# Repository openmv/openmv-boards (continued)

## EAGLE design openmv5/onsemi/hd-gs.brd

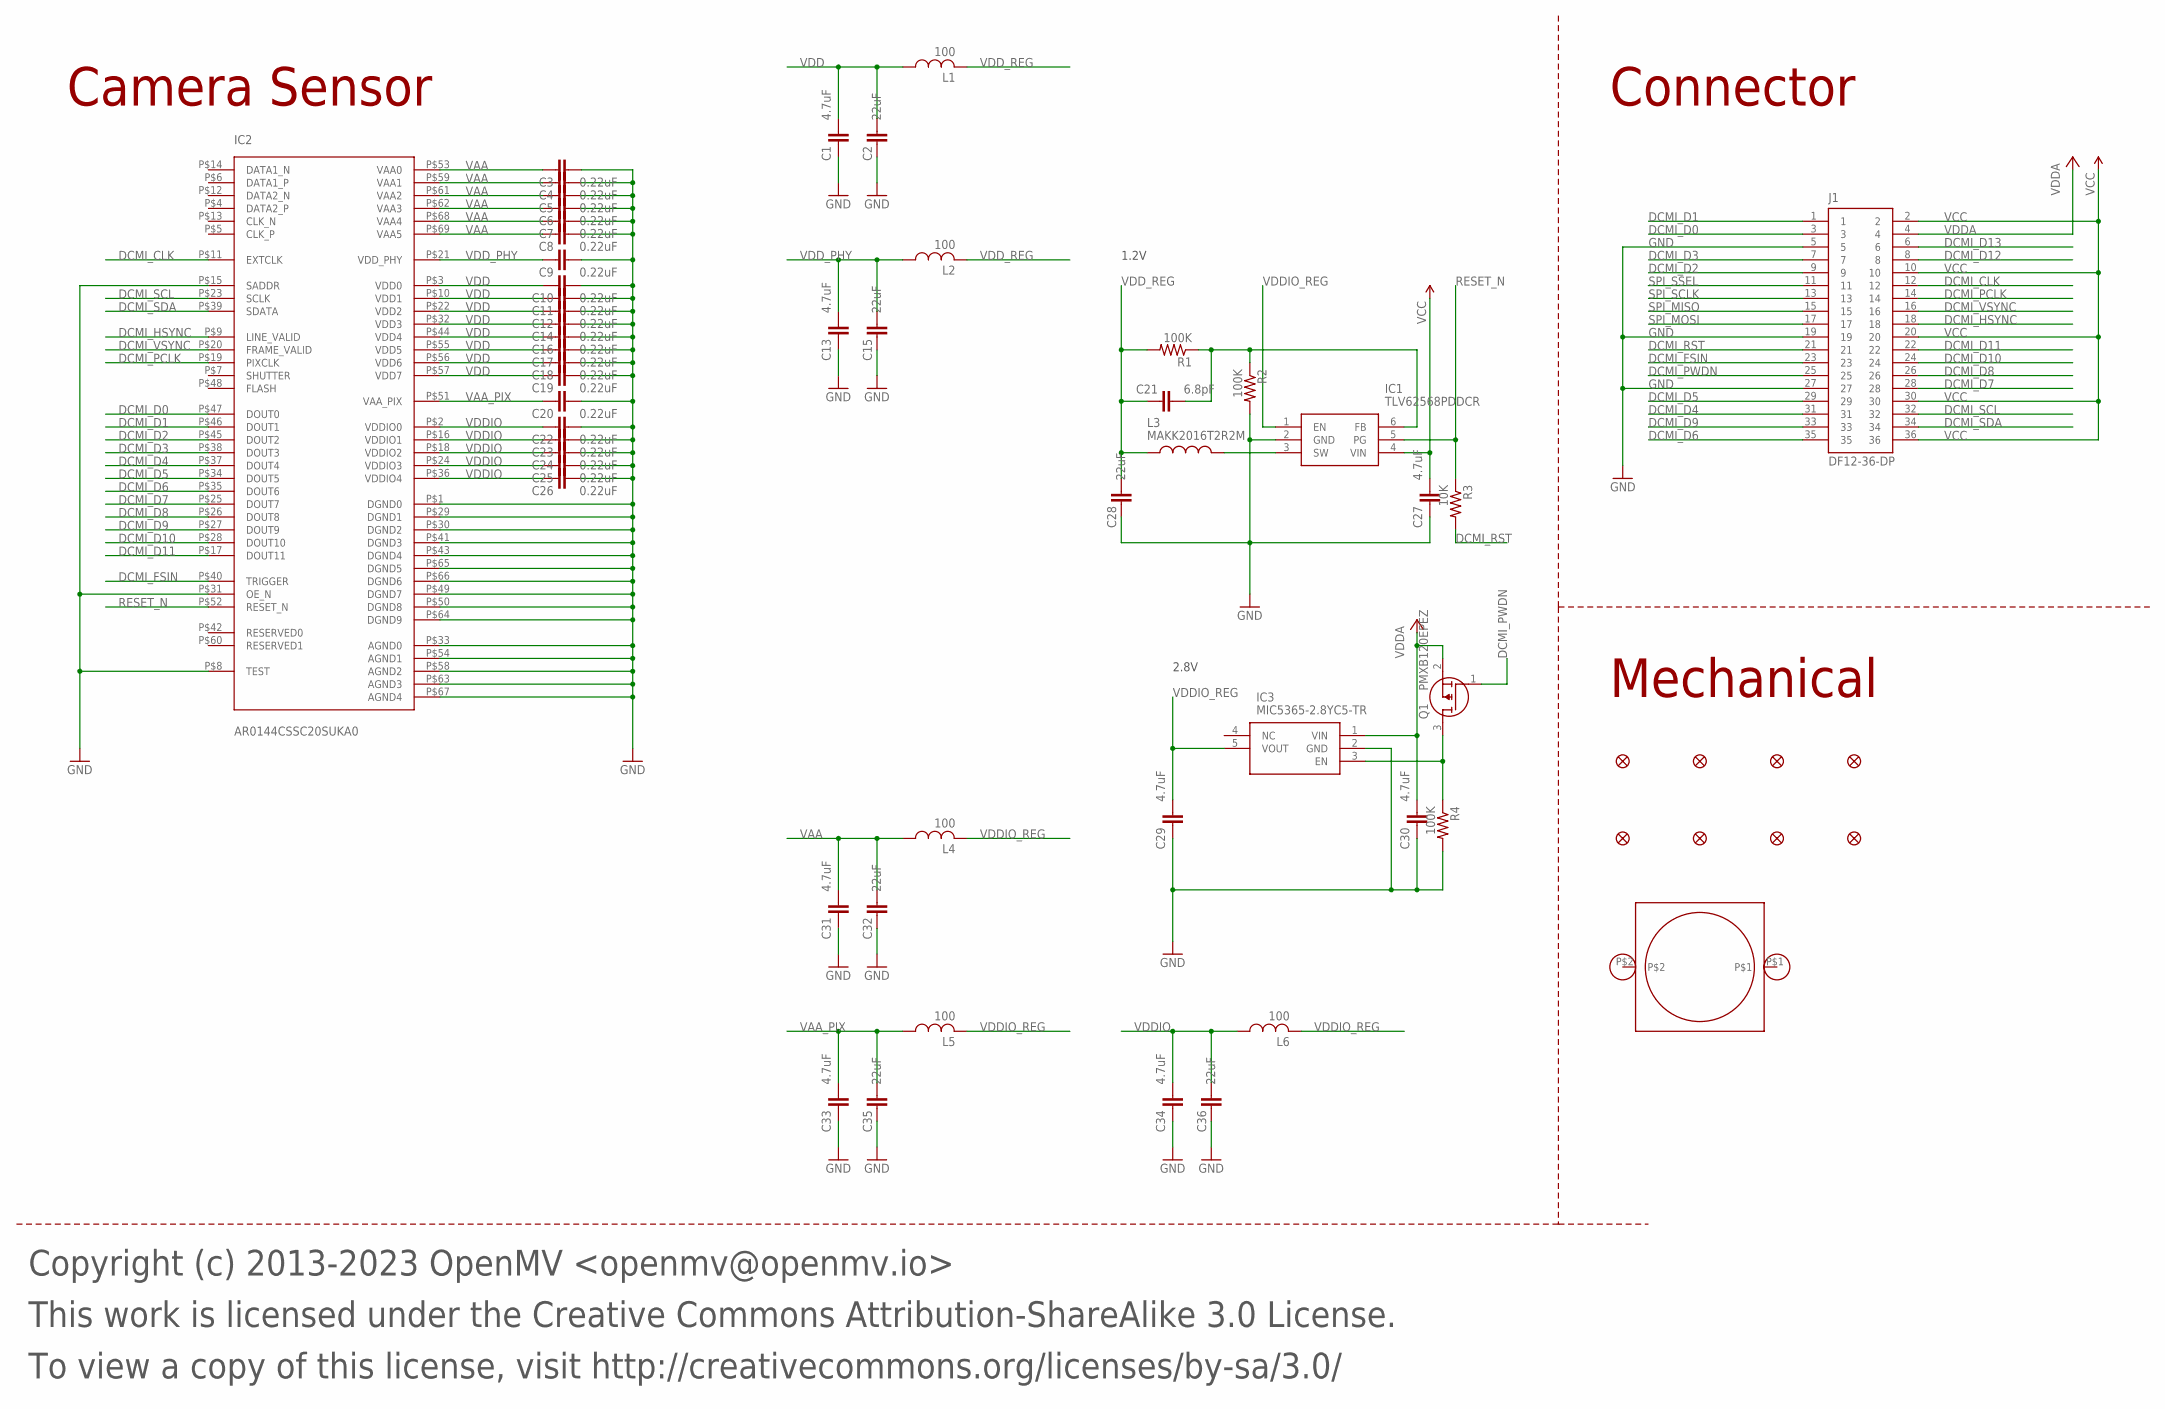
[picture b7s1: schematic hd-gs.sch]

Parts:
C1, C13, C27, C29, C30, C31, C33, C34: 4.7uF; 0402; MPN JMK105BBJ475MV-F
C2, C15, C28, C32, C35, C36: 22uF; 0805; MPN CL21A226MQQNNNE
C3, C4, C5, C6, C7, C8, C9, C10, C11, C12, C14, C16, C17, C18, C19, C20, C22, C23, C24, C25, C26: 0.22uF; C0201; MPN GRM033R60J224ME15D
C21: 6.8pF; 0402; MPN GRM1555C1H6R8DA01D
FD1, FD2, FD3, FD4, FD5, FD6, FD7, FD8: FIDUCIAL1X2; FIDUCIAL-1X2
H1: LENSMOUNT20MM; LENSMOUNT-20MM
IC1: TLV62568PDDCR; SOT95P280X110-6N; MPN TLV62568PDDCR
IC2: AR0144CSSC20SUKA0; MPN AR0144CSSC20SUKA0-CRBR
IC3: MIC5365-2.8YC5-TR; SOT65P210X110-5N; MPN MIC5365-2.8YC5-TR
J1: DF12-36-DP; MPN DF12NB(3.0)-36DP-0.5V(51)
L1, L2, L4, L5, L6: 100; 0402; MPN MFBM1V1005-101-R
L3: MAKK2016T2R2M; INDC2016X100N; MPN MAKK2016T2R2M
Q1: PMXB120EPEZ; MPN PMXB120EPEZ
R1, R2, R4: 100K; R0402; MPN AC0402FR-07100KL
R3: 10K; R0402; MPN AC0402FR-1310KL

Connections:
DCMI_CLK: IC2.P$11 (EXTCLK), J1.12
DCMI_D0: IC2.P$47 (DOUT0), J1.3
DCMI_D1: IC2.P$46 (DOUT1), J1.1
DCMI_D2: IC2.P$45 (DOUT2), J1.9
DCMI_D3: IC2.P$38 (DOUT3), J1.7
DCMI_D4: IC2.P$37 (DOUT4), J1.31
DCMI_D5: IC2.P$34 (DOUT5), J1.29
DCMI_D6: IC2.P$35 (DOUT6), J1.35
DCMI_D7: IC2.P$25 (DOUT7), J1.28
DCMI_D8: IC2.P$26 (DOUT8), J1.26
DCMI_D9: IC2.P$27 (DOUT9), J1.33
DCMI_D10: IC2.P$28 (DOUT10), J1.24
DCMI_D11: IC2.P$17 (DOUT11), J1.22
DCMI_D12: J1.8
DCMI_D13: J1.6
DCMI_FSIN: IC2.P$40 (TRIGGER), J1.23
DCMI_HSYNC: IC2.P$9 (LINE_VALID), J1.18
DCMI_PCLK: IC2.P$19 (PIXCLK), J1.14
DCMI_PWDN: J1.25, Q1.1 (G)
DCMI_PWDN_INT: IC3.3 (EN), Q1.3 (D), R4.1
DCMI_RST: J1.21, R3.2
DCMI_SCL: IC2.P$23 (SCLK), J1.32
DCMI_SDA: IC2.P$39 (SDATA), J1.34
DCMI_VSYNC: IC2.P$20 (FRAME_VALID), J1.16
FB: C21.2, IC1.6 (FB), R1.1, R2.1
GND: C1.1, C2.1, C3.2, C4.2, C5.2, C6.2, C7.2, C8.2, C9.2, C10.2, C11.2, C12.2, C13.1, C14.2, C15.1, C16.2, C17.2, C18.2, C19.2, C20.2, C22.2, C23.2, C24.2, C25.2, C26.2, C27.1, C28.1, C29.1, C30.1, C31.1, C32.1, C33.1, C34.1, C35.1, C36.1, IC1.2 (GND), IC2.P$1 (DGND0), IC2.P$8 (TEST), IC2.P$15 (SADDR), IC2.P$29 (DGND1), IC2.P$30 (DGND2), IC2.P$31 (OE_N), IC2.P$33 (AGND0), IC2.P$41 (DGND3), IC2.P$43 (DGND4), IC2.P$49 (DGND7), IC2.P$50 (DGND8), IC2.P$54 (AGND1), IC2.P$58 (AGND2), IC2.P$63 (AGND3), IC2.P$64 (DGND9), IC2.P$65 (DGND5), IC2.P$66 (DGND6), IC2.P$67 (AGND4), IC3.2 (GND), J1.5, J1.19, J1.27, R2.2, R4.2
RESET_N: IC1.5 (PG), IC2.P$52 (RESET_N), R3.1
SPI_MISO: J1.15
SPI_MOSI: J1.17
SPI_SCLK: J1.13
SPI_SSEL: J1.11
SW: IC1.3 (SW), L3.2
VAA: C3.1, C4.1, C5.1, C6.1, C7.1, C8.1, C31.2, C32.2, IC2.P$53 (VAA0), IC2.P$59 (VAA1), IC2.P$61 (VAA2), IC2.P$62 (VAA3), IC2.P$68 (VAA4), IC2.P$69 (VAA5), L4.1
VAA_PIX: C20.1, C33.2, C35.2, IC2.P$51 (VAA_PIX), L5.1
VCC: C27.2, IC1.4 (VIN), J1.2, J1.10, J1.20, J1.30, J1.36
VDD: C1.2, C2.2, C10.1, C11.1, C12.1, C14.1, C16.1, C17.1, C18.1, C19.1, IC2.P$3 (VDD0), IC2.P$10 (VDD1), IC2.P$22 (VDD2), IC2.P$32 (VDD3), IC2.P$44 (VDD4), IC2.P$55 (VDD5), IC2.P$56 (VDD6), IC2.P$57 (VDD7), L1.1
VDDA: C30.2, IC3.1 (VIN), J1.4, Q1.2 (S)
VDDIO: C22.1, C23.1, C24.1, C25.1, C26.1, C34.2, C36.2, IC2.P$2 (VDDIO0), IC2.P$16 (VDDIO1), IC2.P$18 (VDDIO2), IC2.P$24 (VDDIO3), IC2.P$36 (VDDIO4), L6.1
VDDIO_REG: C29.2, IC1.1 (EN), IC3.5 (VOUT), L4.2, L5.2, L6.2
VDD_PHY: C9.1, C13.2, C15.2, IC2.P$21 (VDD_PHY), L2.1
VDD_REG: C21.1, C28.2, L1.2, L2.2, L3.1, R1.2

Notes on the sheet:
Copyright (c) 2013-2023 OpenMV <openmv@openmv.io>
This work is licensed under the Creative Commons Attribution-ShareAlike 3.0 License.
To view a copy of this license, visit http://creativecommons.org/licenses/by-sa/3.0/
Camera Sensor
Mechanical
Connector
1.2V
2.8V

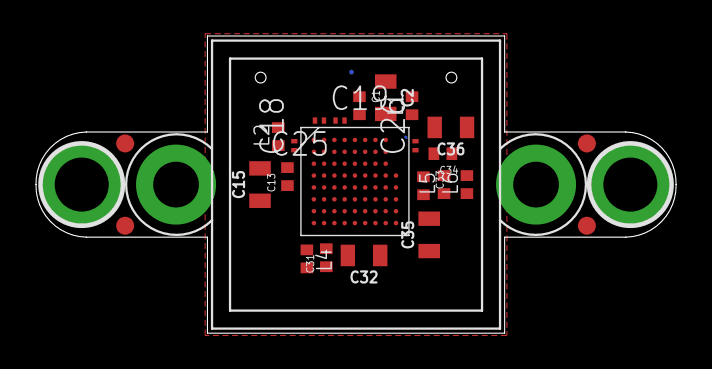
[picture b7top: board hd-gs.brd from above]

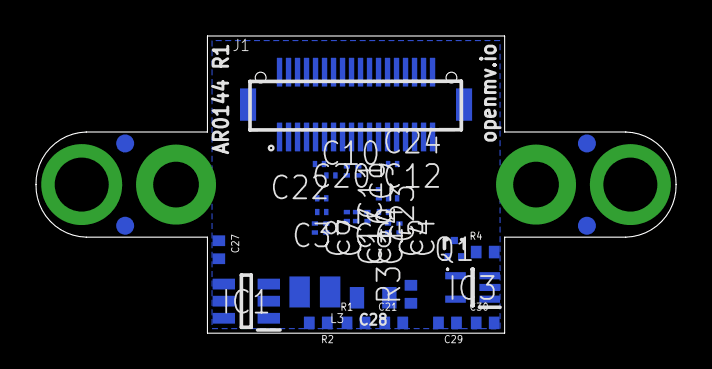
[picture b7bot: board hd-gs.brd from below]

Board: 6 copper layers, 35.6 x 16.5 mm, 60 parts (35 on the bottom side), 35 nets.

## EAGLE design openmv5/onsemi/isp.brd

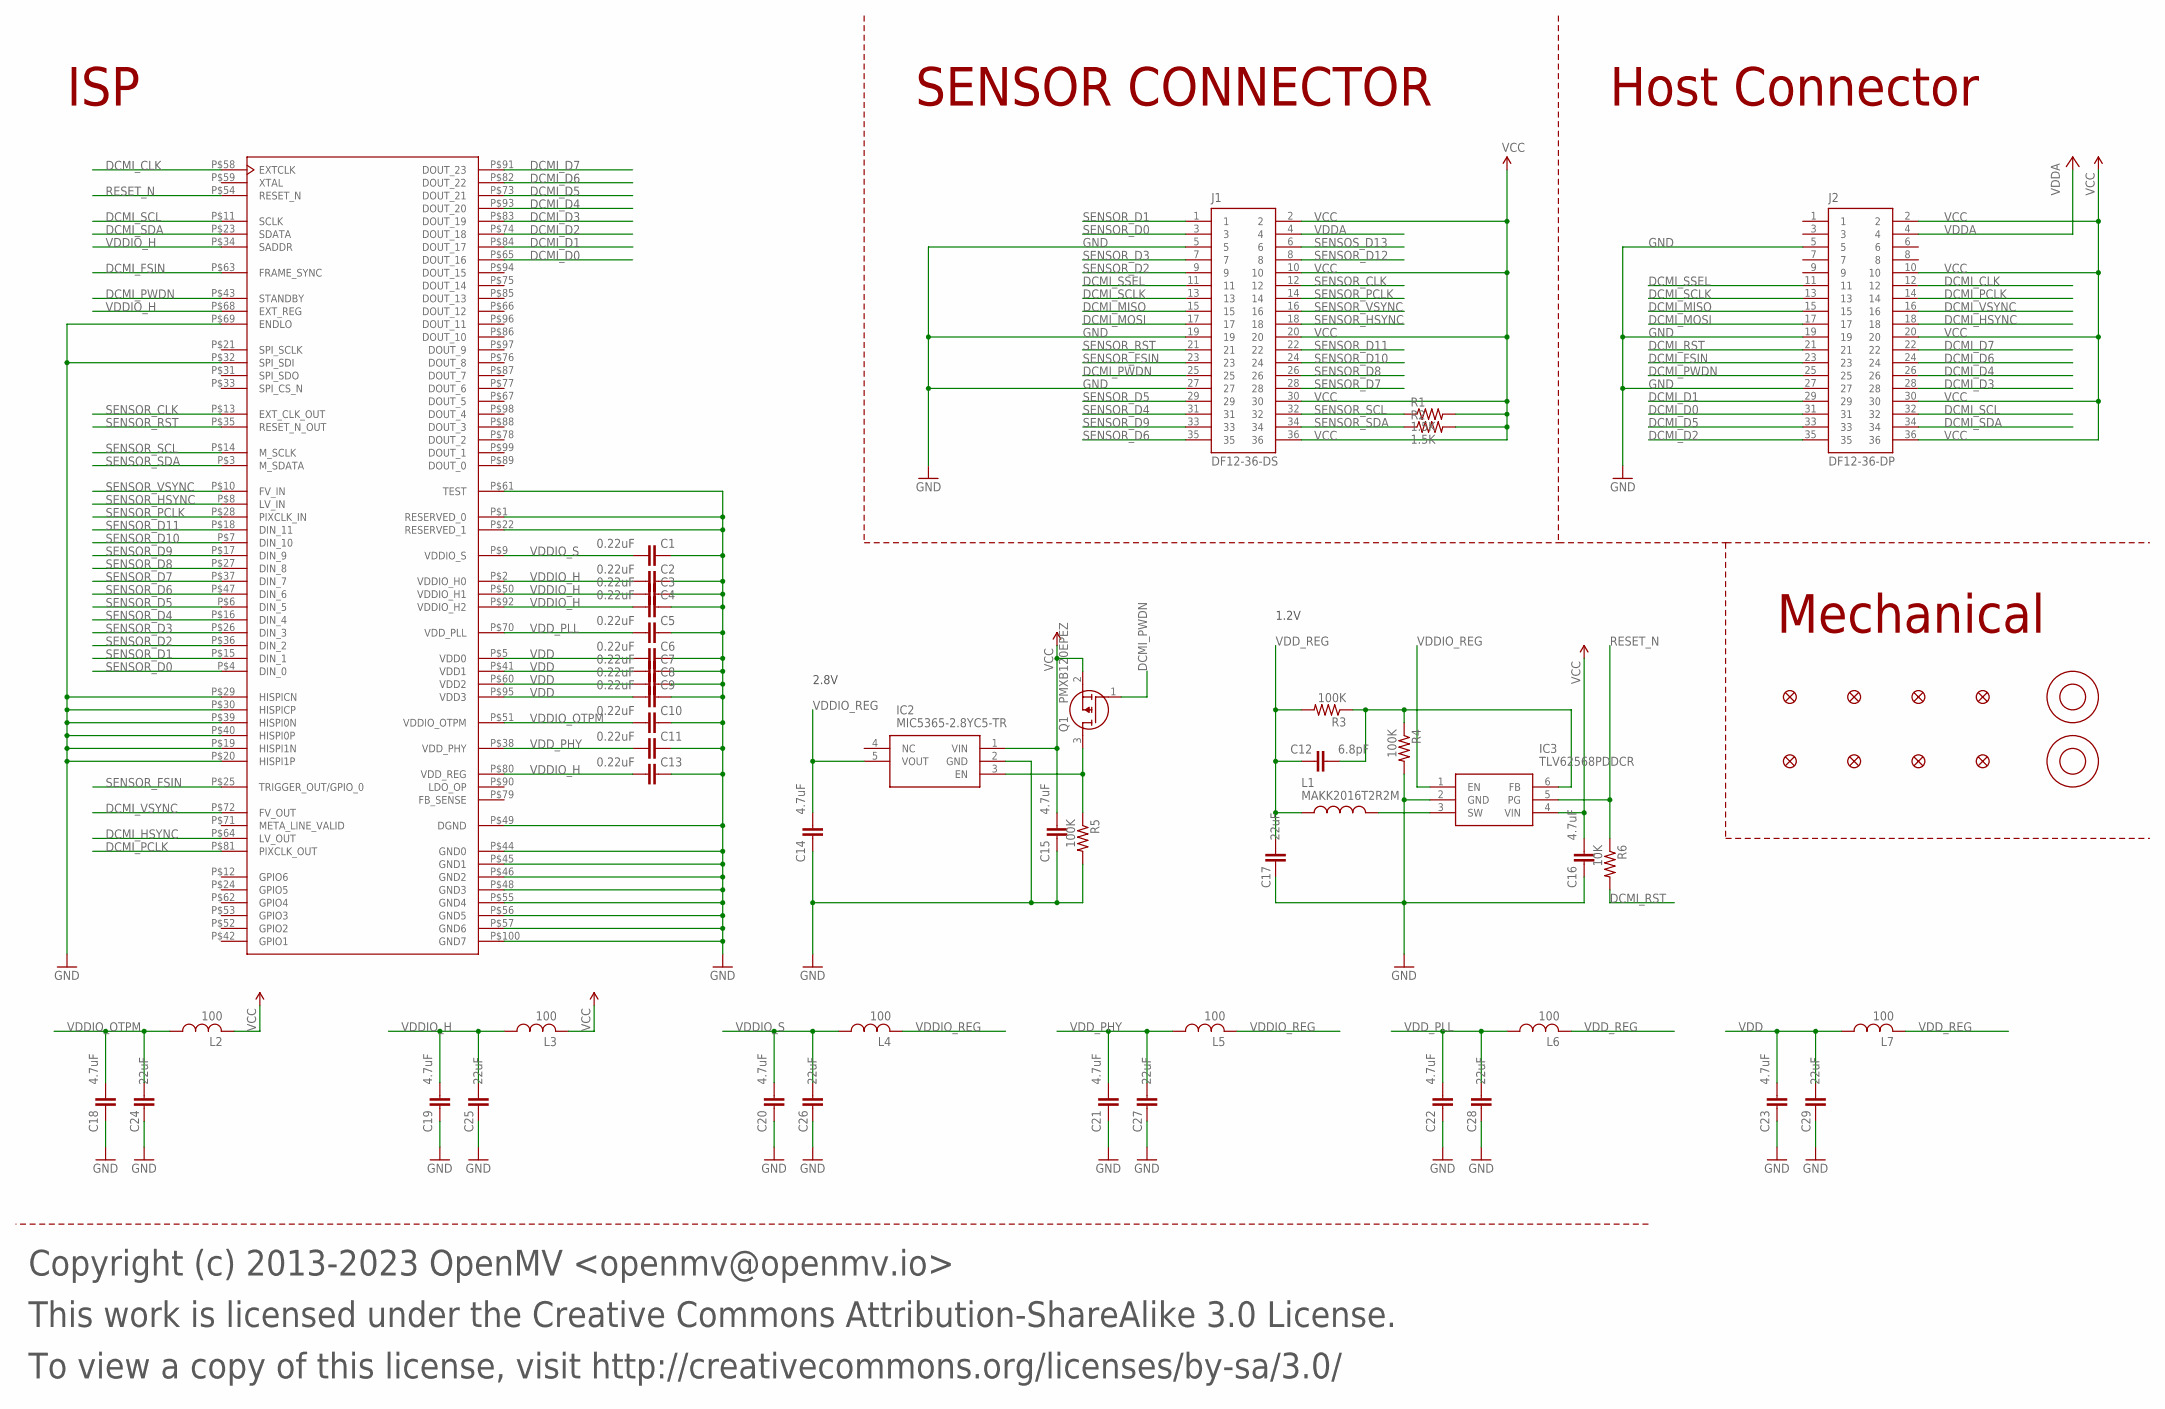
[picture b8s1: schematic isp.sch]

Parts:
C1, C2, C3, C4, C5, C6, C7, C8, C9, C10, C11, C13: 0.22uF; C0201; MPN GRM033R60J224ME15D
C12: 6.8pF; 0402; MPN GRM1555C1H6R8DA01D
C14, C15, C16, C18, C19, C20, C21, C22, C23: 4.7uF; 0402; MPN JMK105BBJ475MV-F
C17, C24, C25, C26, C27, C28, C29: 22uF; 0805; MPN CL21A226MQQNNNE
FD1, FD2, FD3, FD4, FD5, FD6, FD7, FD8: FIDUCIAL1X2; FIDUCIAL-1X2
IC1: AP0202AT2L00XPGA0; MPN AP0202AT2L00XPGA0-DR
IC2: MIC5365-2.8YC5-TR; SOT65P210X110-5N; MPN MIC5365-2.8YC5-TR
IC3: TLV62568PDDCR; SOT95P280X110-6N; MPN TLV62568PDDCR
J1: DF12-36-DS; MPN DF12NB-36DS-0.5V(51)
J2: DF12-36-DP; MPN DF12NB(3.0)-36DP-0.5V(51)
L1: MAKK2016T2R2M; INDC2016X100N; MPN MAKK2016T2R2M
L2, L3, L4, L5, L6, L7: 100; 0402; MPN MFBM1V1005-101-R
M1, M2: 9774030151R; MPN 9774030151R
Q1: PMXB120EPEZ; MPN PMXB120EPEZ
R1, R2: 1.5K; R0402; MPN RC0402FR-131K5L
R3, R4, R5: 100K; R0402; MPN AC0402FR-07100KL
R6: 10K; R0402; MPN AC0402FR-1310KL

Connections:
DCMI_CLK: IC1.P$58 (EXTCLK), J2.12
DCMI_D0: IC1.P$65 (DOUT_16), J2.31
DCMI_D1: IC1.P$84 (DOUT_17), J2.29
DCMI_D2: IC1.P$74 (DOUT_18), J2.35
DCMI_D3: IC1.P$83 (DOUT_19), J2.28
DCMI_D4: IC1.P$93 (DOUT_20), J2.26
DCMI_D5: IC1.P$73 (DOUT_21), J2.33
DCMI_D6: IC1.P$82 (DOUT_22), J2.24
DCMI_D7: IC1.P$91 (DOUT_23), J2.22
DCMI_FSIN: IC1.P$63 (FRAME_SYNC), J2.23
DCMI_HSYNC: IC1.P$64 (LV_OUT), J2.18
DCMI_MISO: J1.15, J2.15
DCMI_MOSI: J1.17, J2.17
DCMI_PCLK: IC1.P$81 (PIXCLK_OUT), J2.14
DCMI_PWDN: IC1.P$43 (STANDBY), J1.25, J2.25, Q1.1 (G)
DCMI_PWDN_INT: IC2.3 (EN), Q1.3 (D), R5.1
DCMI_RST: J2.21, R6.2
DCMI_SCL: IC1.P$11 (SCLK), J2.32
DCMI_SCLK: J1.13, J2.13
DCMI_SDA: IC1.P$23 (SDATA), J2.34
DCMI_SSEL: J1.11, J2.11
DCMI_VSYNC: IC1.P$72 (FV_OUT), J2.16
FB: C12.2, IC3.6 (FB), R3.1, R4.1
GND: C1.1, C2.1, C3.1, C4.1, C5.1, C6.1, C7.1, C8.1, C9.1, C10.1, C11.1, C13.1, C14.1, C15.1, C16.1, C17.1, C18.1, C19.1, C20.1, C21.1, C22.1, C23.1, C24.1, C25.1, C26.1, C27.1, C28.1, C29.1, IC1.P$1 (RESERVED_0), IC1.P$19 (HISPI1N), IC1.P$20 (HISPI1P), IC1.P$22 (RESERVED_1), IC1.P$29 (HISPICN), IC1.P$30 (HISPICP), IC1.P$32 (SPI_SDI), IC1.P$39 (HISPI0N), IC1.P$40 (HISPI0P), IC1.P$44 (GND0), IC1.P$45 (GND1), IC1.P$46 (GND2), IC1.P$48 (GND3), IC1.P$49 (DGND), IC1.P$55 (GND4), IC1.P$56 (GND5), IC1.P$57 (GND6), IC1.P$61 (TEST), IC1.P$69 (ENDLO), IC1.P$100 (GND7), IC2.2 (GND), IC3.2 (GND), J1.5, J1.19, J1.27, J2.5, J2.19, J2.27, R4.2, R5.2
RESET_N: IC1.P$54 (RESET_N), IC3.5 (PG), R6.1
SENSOR_CLK: IC1.P$13 (EXT_CLK_OUT), J1.12
SENSOR_D0: IC1.P$4 (DIN_0), J1.3
SENSOR_D1: IC1.P$15 (DIN_1), J1.1
SENSOR_D2: IC1.P$36 (DIN_2), J1.9
SENSOR_D3: IC1.P$26 (DIN_3), J1.7
SENSOR_D4: IC1.P$16 (DIN_4), J1.31
SENSOR_D5: IC1.P$6 (DIN_5), J1.29
SENSOR_D6: IC1.P$47 (DIN_6), J1.35
SENSOR_D7: IC1.P$37 (DIN_7), J1.28
SENSOR_D8: IC1.P$27 (DIN_8), J1.26
SENSOR_D9: IC1.P$17 (DIN_9), J1.33
SENSOR_D10: IC1.P$7 (DIN_10), J1.24
SENSOR_D11: IC1.P$18 (DIN_11), J1.22
SENSOR_D12: J1.8
SENSOR_FSIN: IC1.P$25 (TRIGGER_OUT/GPIO_0), J1.23
SENSOR_HSYNC: IC1.P$8 (LV_IN), J1.18
SENSOR_PCLK: IC1.P$28 (PIXCLK_IN), J1.14
SENSOR_RST: IC1.P$35 (RESET_N_OUT), J1.21
SENSOR_SCL: IC1.P$14 (M_SCLK), J1.32, R1.1
SENSOR_SDA: IC1.P$3 (M_SDATA), J1.34, R2.1
SENSOR_VSYNC: IC1.P$10 (FV_IN), J1.16
SENSOS_D13: J1.6
SW: IC3.3 (SW), L1.2
VCC: C15.2, C16.2, IC2.1 (VIN), IC3.4 (VIN), J1.2, J1.10, J1.20, J1.30, J1.36, J2.2, J2.10, J2.20, J2.30, J2.36, L2.2, L3.2, Q1.2 (S), R1.2, R2.2
VDD: C6.2, C7.2, C8.2, C9.2, C23.2, C29.2, IC1.P$5 (VDD0), IC1.P$41 (VDD1), IC1.P$60 (VDD2), IC1.P$95 (VDD3), L7.1
VDDA: J1.4, J2.4
VDDIO_H: C2.2, C3.2, C4.2, C13.2, C19.2, C25.2, IC1.P$2 (VDDIO_H0), IC1.P$34 (SADDR), IC1.P$50 (VDDIO_H1), IC1.P$68 (EXT_REG), IC1.P$80 (VDD_REG), IC1.P$92 (VDDIO_H2), L3.1
VDDIO_OTPM: C10.2, C18.2, C24.2, IC1.P$51 (VDDIO_OTPM), L2.1
VDDIO_REG: C14.2, IC2.5 (VOUT), IC3.1 (EN), L4.2, L5.2
VDDIO_S: C1.2, C20.2, C26.2, IC1.P$9 (VDDIO_S), L4.1
VDD_PHY: C11.2, C21.2, C27.2, IC1.P$38 (VDD_PHY), L5.1
VDD_PLL: C5.2, C22.2, C28.2, IC1.P$70 (VDD_PLL), L6.1
VDD_REG: C12.1, C17.2, L1.1, L6.2, L7.2, R3.2

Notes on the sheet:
Copyright (c) 2013-2023 OpenMV <openmv@openmv.io>
This work is licensed under the Creative Commons Attribution-ShareAlike 3.0 License.
To view a copy of this license, visit http://creativecommons.org/licenses/by-sa/3.0/
ISP
Mechanical
Host Connector
1.2V
2.8V
SENSOR CONNECTOR

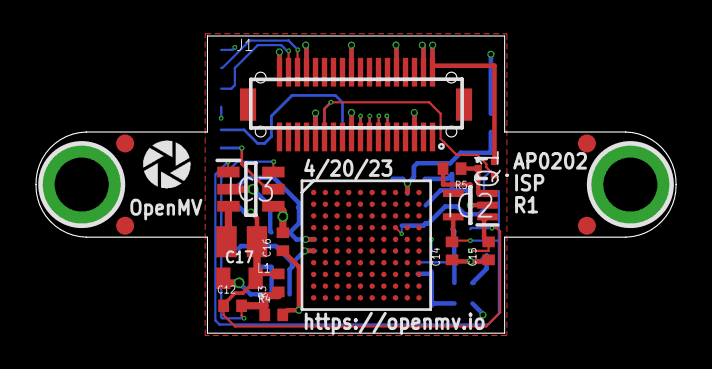
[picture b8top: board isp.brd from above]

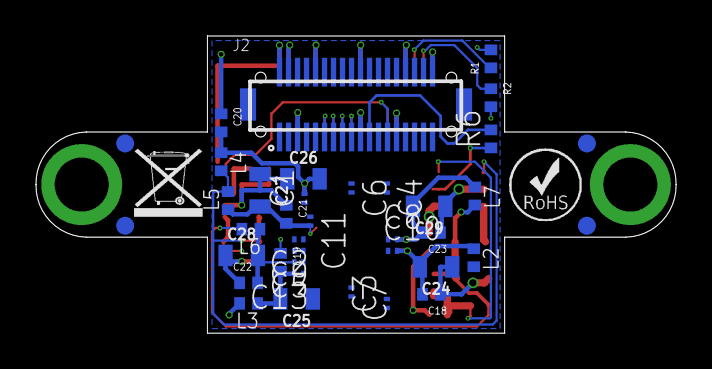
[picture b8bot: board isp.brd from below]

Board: 6 copper layers, 35.6 x 16.5 mm, 61 parts (40 on the bottom side), 56 nets.

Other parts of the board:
U$1: WEEE
U$2: ROHS
U$9: OPENMV-LOGO

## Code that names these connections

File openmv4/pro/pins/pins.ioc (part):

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Mcu.Name=STM32H743IIKx
Mcu.Package=UFBGA176
Mcu.UserName=STM32H743IIKx
PA0.Signal=S_TIM2_CH1
PA1.Signal=S_TIM2_CH2
PA10.Mode=Slave_8_bits_External_Synchro
PA10.Signal=DCMI_D1
PA11.Mode=NSS_Signal_Hard_Output
PA11.Signal=SPI2_NSS
PA12.Mode=Full_Duplex_Master
PA12.Signal=SPI2_SCK
PA13\ (JTMS/SWDIO).Mode=Serial_Wire
PA13\ (JTMS/SWDIO).Signal=DEBUG_JTMS-SWDIO
PA14\ (JTCK/SWCLK).Mode=Serial_Wire
PA14\ (JTCK/SWCLK).Signal=DEBUG_JTCK-SWCLK
PA15\ (JTDI).Mode=NSS_Signal_Hard_Output
PA15\ (JTDI).Signal=SPI6_NSS
PA2.Signal=S_TIM2_CH3
PA3.Mode=Device_HS
PA3.Signal=USB_OTG_HS_ULPI_D0
PA4.Mode=Slave_8_bits_External_Synchro
PA4.Signal=DCMI_HSYNC
PA5.Mode=Device_HS
PA5.Signal=USB_OTG_HS_ULPI_CK
PA6.Mode=Slave_8_bits_External_Synchro
PA6.Signal=DCMI_PIXCLK
PA7.Signal=FMC_SDNWE
PA8.Signal=S_TIM1_CH1
PA9.Mode=Slave_8_bits_External_Synchro
PA9.Signal=DCMI_D0
PB0.Mode=Device_HS
PB0.Signal=USB_OTG_HS_ULPI_D1
PB1.Mode=Device_HS
PB1.Signal=USB_OTG_HS_ULPI_D2
PB10.Mode=Device_HS
PB10.Signal=USB_OTG_HS_ULPI_D3
PB11.Mode=Device_HS
PB11.Signal=USB_OTG_HS_ULPI_D4
PB12.Mode=Device_HS
PB12.Signal=USB_OTG_HS_ULPI_D5
PB13.Mode=Device_HS
PB13.Signal=USB_OTG_HS_ULPI_D6
PB14.Mode=SD_4_bits_Wide_bus
PB14.Signal=SDMMC2_D0
PB15.Mode=SD_4_bits_Wide_bus
PB15.Signal=SDMMC2_D1
PB2.GPIOParameters=GPIO_Label
PB2.GPIO_Label=WL_REG_ON
PB2.Signal=GPIO_Output
PB3\ (JTDO/TRACESWO).Mode=SD_4_bits_Wide_bus
PB3\ (JTDO/TRACESWO).Signal=SDMMC2_D2
PB4\ (NJTRST).Mode=SD_4_bits_Wide_bus
PB4\ (NJTRST).Signal=SDMMC2_D3
PB5.Mode=Device_HS
PB5.Signal=USB_OTG_HS_ULPI_D7
PB6.Mode=I2C
PB6.Signal=I2C4_SCL
PB7.Mode=I2C
PB7.Signal=I2C4_SDA
PB8.Mode=I2C
PB8.Signal=I2C1_SCL
PB9.Mode=I2C
PB9.Signal=I2C1_SDA
PC0.Mode=Device_HS
PC0.Signal=USB_OTG_HS_ULPI_STP
PC1.Mode=Full_Duplex_Master
PC1.Signal=SPI2_MOSI
PC10.Mode=SD_4_bits_Wide_bus
PC10.Signal=SDMMC1_D2
PC11.Mode=SD_4_bits_Wide_bus
PC11.Signal=SDMMC1_D3
PC12.Mode=SD_4_bits_Wide_bus
PC12.Signal=SDMMC1_CK
PC13.GPIOParameters=GPIO_Label
PC13.GPIO_Label=DCMI_RST
PC13.Signal=GPIO_Output
PC14-OSC32_IN\ (OSC32_IN).Mode=LSE-External-Clock-Source
PC14-OSC32_IN\ (OSC32_IN).Signal=RCC_OSC32_IN
PC15-OSC32_OUT\ (OSC32_OUT).GPIOParameters=GPIO_Label
PC15-OSC32_OUT\ (OSC32_OUT).GPIO_Label=USBEN
PC15-OSC32_OUT\ (OSC32_OUT).Signal=GPIO_Output
PC2_C.Mode=Full_Duplex_Master
PC2_C.Signal=SPI2_MISO
PC3_C.Mode=Device_HS
PC3_C.Signal=USB_OTG_HS_ULPI_NXT
PC4.GPIOParameters=GPIO_Label
PC4.GPIO_Label=WL_HOST_WAKE
PC4.Signal=GPIO_Output
PC5.Signal=ADCx_INP8
PC6.Signal=S_TIM3_CH1
PC7.Signal=S_TIM3_CH2
PC8.Mode=SD_4_bits_Wide_bus
PC8.Signal=SDMMC1_D0
PC9.Mode=SD_4_bits_Wide_bus
PC9.Signal=SDMMC1_D1
PD0.Signal=FMC_D2_DA2
PD1.Signal=FMC_D3_DA3
PD10.Signal=FMC_D15_DA15
PD11.Mode=Single Bank 1
PD11.Signal=QUADSPI_BK1_IO0
PD12.Mode=Single Bank 1
PD12.Signal=QUADSPI_BK1_IO1
PD13.Mode=Single Bank 1
PD13.Signal=QUADSPI_BK1_IO3
PD14.Signal=FMC_D0_DA0
PD15.Signal=FMC_D1_DA1
PD2.Mode=SD_4_bits_Wide_bus
PD2.Signal=SDMMC1_CMD
PD3.Mode=Slave_8_bits_External_Synchro
PD3.Signal=DCMI_D5
PD4.GPIOParameters=GPIO_Label
PD4.GPIO_Label=P9
PD4.Signal=GPIO_Output
PD5.GPIOParameters=GPIO_Label
PD5.GPIO_Label=P10
PD5.Signal=GPIO_Output
PD6.Mode=SD_4_bits_Wide_bus
PD6.Signal=SDMMC2_CK
PD7.Mode=SD_4_bits_Wide_bus
PD7.Signal=SDMMC2_CMD
PD8.Signal=FMC_D13_DA13
PD9.Signal=FMC_D14_DA14
PE0.Signal=FMC_NBL0
PE1.Signal=FMC_NBL1
PE10.Signal=FMC_D7_DA7
PE11.Signal=FMC_D8_DA8
PE12.Signal=FMC_D9_DA9
PE13.Signal=FMC_D10_DA10
PE14.Signal=FMC_D11_DA11
PE15.Signal=FMC_D12_DA12
PE2.Mode=Single Bank 1
PE2.Signal=QUADSPI_BK1_IO2
PE3.GPIOParameters=GPIO_Label
PE3.GPIO_Label=BT_REG_ON
PE3.Signal=GPIO_Output
PE4.Mode=Slave_8_bits_External_Synchro
PE4.Signal=DCMI_D4
PE5.Mode=Slave_8_bits_External_Synchro
PE5.Signal=DCMI_D6
PE6.Mode=Slave_8_bits_External_Synchro
PE6.Signal=DCMI_D7
PE7.Signal=FMC_D4_DA4
PE8.Signal=FMC_D5_DA5
PE9.Signal=FMC_D6_DA6
PF0.Signal=FMC_A0
PF1.Signal=FMC_A1
PF10.Mode=Single Bank 1
PF10.Signal=QUADSPI_CLK
PF11.Signal=FMC_SDNRAS
PF12.Signal=FMC_A6
PF13.Signal=FMC_A7
PF14.Signal=FMC_A8
PF15.Signal=FMC_A9
PF2.Signal=FMC_A2
PF3.Signal=FMC_A3
PF4.Signal=FMC_A4
PF5.Signal=FMC_A5
PF6.Mode=Asynchronous
PF6.Signal=UART7_RX
PF7.Mode=Asynchronous
PF7.Signal=UART7_TX
PF8.Mode=CTS_RTS
PF8.Signal=UART7_RTS
PF9.Mode=CTS_RTS
PF9.Signal=UART7_CTS
PG0.Signal=FMC_A10
PG1.Signal=FMC_A11
PG10.Mode=Slave_8_bits_External_Synchro
PG10.Signal=DCMI_D2
PG11.Mode=Slave_8_bits_External_Synchro
PG11.Signal=DCMI_D3
PG12.Mode=Full_Duplex_Master
PG12.Signal=SPI6_MISO
PG13.Mode=Full_Duplex_Master
PG13.Signal=SPI6_SCK
PG14.Mode=Full_Duplex_Master
PG14.Signal=SPI6_MOSI
PG15.Signal=FMC_SDNCAS
PG2.GPIOParameters=GPIO_Speed,GPIO_Label
PG2.GPIO_Label=CRYPTOEN
PG2.GPIO_Speed=GPIO_SPEED_FREQ_LOW
PG2.Signal=GPIO_Output
PG3.GPIOParameters=GPIO_Label
PG3.GPIO_Label=BT_HOST_WAKE
PG3.Signal=GPIO_Output
PG4.Signal=FMC_A14_BA0
PG5.Signal=FMC_A15_BA1
PG6.Mode=Single Bank 1
PG6.Signal=QUADSPI_BK1_NCS
PG7.GPIOParameters=GPIO_Label
PG7.GPIO_Label=SD_CD
PG7.Signal=GPIO_Input
PG8.Signal=FMC_SDCLK
PG9.Mode=Slave_8_bits_External_Synchro
PG9.Signal=DCMI_VSYNC
PH0-OSC_IN\ (PH0).Mode=HSE-External-Clock-Source
PH0-OSC_IN\ (PH0).Signal=RCC_OSC_IN
PH1-OSC_OUT\ (PH1).GPIOParameters=GPIO_Label
PH1-OSC_OUT\ (PH1).GPIO_Label=OSCEN
PH1-OSC_OUT\ (PH1).Signal=GPIO_Output
PH10.Signal=FMC_D18
PH11.Signal=FMC_D19
PH12.Signal=FMC_D20
PH13.Signal=FMC_D21
PH14.Signal=FMC_D22
PH15.Signal=FMC_D23
PH2.Mode=SdramChipSelect1_1
PH2.Signal=FMC_SDCKE0
PH3.Mode=SdramChipSelect1_1
PH3.Signal=FMC_SDNE0
PH4.Mode=I2C
PH4.Signal=I2C2_SCL
PH5.Mode=I2C
PH5.Signal=I2C2_SDA
PH6.Signal=S_TIM12_CH1
PH7.GPIOParameters=GPIO_Label
PH7.GPIO_Label=BT_DEV_WAKE
PH7.Signal=GPIO_Output
PH8.Signal=FMC_D16
PH9.Signal=FMC_D17
PI0.Signal=FMC_D24
PI1.Signal=FMC_D25
PI10.Signal=FMC_D31
PI11.Mode=Device_HS
PI11.Signal=USB_OTG_HS_ULPI_DIR
PI2.Signal=FMC_D26
PI3.Signal=FMC_D27
PI4.Signal=FMC_NBL2
PI5.Signal=FMC_NBL3
PI6.Signal=FMC_D28
PI7.Signal=FMC_D29
PI8.GPIOParameters=GPIO_Label
PI8.GPIO_Label=DCMI_PWDN
PI8.Signal=GPIO_Output
PI9.Signal=FMC_D30
RCC.HSE_VALUE=24000000
RCC.SYSCLKFreq_VALUE=480000000
RCC.SYSCLKSource=RCC_SYSCLKSOURCE_PLLCLK
board=custom

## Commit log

2018-02-17 Add design files.
2018-02-17 Add case design file.
2018-02-17 Move case to cad dir.
2018-02-17 Add license file.
2018-02-17 Add Eagle libraries.
2018-02-17 Moved Eagle library to top dir.
2018-08-25 Add datasheets
2018-09-03 upload uart shield
    cp2104 shield
2018-10-27 add sensor shield
    add sensor shield
2018-11-13 Add an adapter shield for D1 Mini shields.
    This adapter lets you use shields designed for the D1 Mini board.
2019-01-21 Add uart board pdf
2019-01-21 Add sensor.pdf
2019-01-21 Add pan and tilt
2019-01-22 Add can shield
2019-01-22 Add RS232 shield
2019-02-09 Fix rs232 shield
2019-03-24 Add OpenMV4 design files.
2019-03-30 add tv shield
2019-03-30 add pdf
2019-03-30 Add TV shield (#7)
    * Add TV shield design files
2019-04-19 Add h7 case
2019-12-01 Add new camera snesors
2019-12-01 Add plus
2019-12-01 Add schematic
2019-12-30 add light shield
2020-02-10 Updated OV5640 circuit
2021-05-31 Add alternative base design
2021-05-31 Add plus alt board design
2021-06-02 PureEngineering Updates
2021-06-02 Signals must be redone
2021-12-28 Add OpenMV Cam Pro design
2021-12-29 Fix wifi power and tof location
2022-01-07 Add MT9V024
2022-01-31 Fixed QSPI pins
2022-01-31 Add mp
2022-01-31 Update design
2022-01-31 Update pro
2022-02-24 Fix pin naming
2022-02-24 Update pro design
2022-03-08 Remove NXP chip
2022-04-02 Fix pin not connected to VCC
2022-04-18 Update the Pro witht he 8x8 ToF
2022-10-29 Update pro design with fixes
2022-10-29 Update pro schematics
2022-12-05 Update jumpers to 0 ohm
2023-02-23 Add AF sensor board
2023-03-10 Add rt files
2023-03-22 Add rt10 design - not routed
2023-03-24 Move pin files
2023-03-26 Add poe shield
2023-03-26 Rename folder
2023-03-26 Delete
2023-03-27 Add labels to PoE shield
2023-03-27 Fix reverse protection on VIN, add TVS on FSIN, and fix USB current limits
2023-03-31 Update PoE Shield heat transfer and add PIR Shield
2023-03-31 Renumber parts
2023-04-01 Final
2023-04-05 Fix wrogn resistor
2023-04-05 Remove 0201 caps
2023-04-05 Add bypasses
2023-04-05 Cleanup label
2023-04-05 Cleanup labels again
2023-04-05 Adjust labels again
2023-04-06 Final PIR shield, fixed regulator
2023-04-06 Fix issues with part selection
2023-04-07 Update remaining MPNs
2023-04-07 Try again
2023-04-07 Add more options
2023-04-07 cleanup silk
2023-04-08 Add CAN/RS232 shield
2023-04-08 Fix part
2023-04-08 Update part
2023-04-10 Add solid works models
2023-04-12 Fix wrong regulator MPN
2023-04-12 Remove 0201 components
2023-04-12 Fix inductor size
2023-04-13 Change inductor to something smaller
2023-04-13 Update cap value
2023-04-14 Add RS442/RS485 shield
2023-04-14 Fix labeling
2023-04-14 Adjust labels
2023-04-14 Fix part and add 3D
2023-04-17 Add driver shield
2023-04-17 Fix wrong resistor value
2023-04-17 Finish up driver shield
2023-04-17 Fix placement
2023-04-17 Fix drc issues
2023-04-18 Add relay shield
2023-04-18 Fix wire stubs
2023-04-19 Fix wrong inductor in PoE
2023-04-22 Add HDR camera concept
2023-04-22 Update resistor value
2023-04-25 Add more cameras
2023-04-25 Remove old files
2023-04-26 Finish out new onsemi cameras
2023-04-30 Add servo shield
2023-04-30 Fix servo shield part
2023-05-11 Remove zener diode from ADC circuit
2023-05-16 Add rev2
2023-05-16 Rename versions
2023-05-16 Update boards
2023-05-16 Rename with specific version
2023-05-16 Update pins
2023-05-17 Update R2 board per all feedback so far
2023-05-17 Update pin to GPIO
2023-05-17 Evaluate power off issues and fix
2023-05-17 Fx leakage issue
2023-05-17 Fix processor name
2023-05-17 Fix missing pages
2023-05-18 Fix label issues
2023-05-18 Fix labels
2023-05-18 Make the last two I/O pins more configurable
2023-05-22 Cleanup
2023-05-27 Update the Design with the new crypto chip
2023-05-31 Fix some issues with MPN and extra lablels
2023-06-02 Update diodes
2023-06-05 Fix possible low power mode leakage
2023-06-05 Update processor
2023-06-05 Update camera modules to use different non-flippable pmosfet
2026-04-25 Add initial board definitions, models, and pinouts
2026-04-25 Remove version.txt, use git tags for versioning
2026-04-26 Add workflow to trigger openmv-studio resources update on tag push
2026-04-27 ci: Trigger studio resources update on main pushes too.
2026-04-29 Update N6 model and pinout.
2026-05-01 Update boards.
    Add romfs info.
